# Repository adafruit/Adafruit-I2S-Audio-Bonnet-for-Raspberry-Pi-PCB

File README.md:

## Adafruit I2S Audio Bonnet for Raspberry Pi - UDA1334A PCB

<a href="http://www.adafruit.com/products/4037"><br/>
Click here to purchase one from the Adafruit shop</a>

PCB files for the Adafruit I2S Audio Bonnet for Raspberry Pi - UDA1334A. Format is EagleCAD schematic and board layout
* https://www.adafruit.com/product/4037

### Description

Add some easy-listenin' tunes to your Raspberry Pi using this basic audio bonnet. It'll give you stereo line out from a digital I2S converter for a good price, and sounds nice to boot! This bonnet features the UDA1334A I2S Stereo DAC, a perfect match for any I2S-output audio interface. It's affordable but sounds great - music to our ears.

It's the exact same size as a Raspberry Pi Zero but works with **any and all** Raspberry Pi computers with a 2x20 connector - A+, B+, Zero, Pi 2, Pi 3, etc. We've tested it out with Raspbian (the official operating system) and Retropie.

This Bonnet uses I2S a digital sound standard, so you get really crisp audio. The digital data goes right into the amplifier so there's no static like you hear from the onboard headphone jack. And it's super easy to get started. Just plug in any line level output into powered speakers or audio system. You can plug in headphones but you'll get some distortion - so its best used into something that is expecting line level out

Each order comes as a fully tested and assembled PCB with a 2x20 socket connector. No soldering required! [Plug it right onto your pi, install the script and reboot](https://learn.adafruit.com/adafruit-i2s-audio-bonnet-for-raspberry-pi). Pow, you're makin' lovely sounds. Want an RCA jack output? [We have a solder-in-able stereo jack as a separate component](https://www.adafruit.com/product/4171)

**Pi Zero, audio cable & speakers not included!**

### License

Adafruit invests time and resources providing this open source design, please support Adafruit and open-source hardware by purchasing products from [Adafruit](https://www.adafruit.com)!

Designed by Limor Fried/Ladyada for Adafruit Industries.

Creative Commons Attribution/Share-Alike, all text above must be included in any redistribution. See license.txt for additional details.

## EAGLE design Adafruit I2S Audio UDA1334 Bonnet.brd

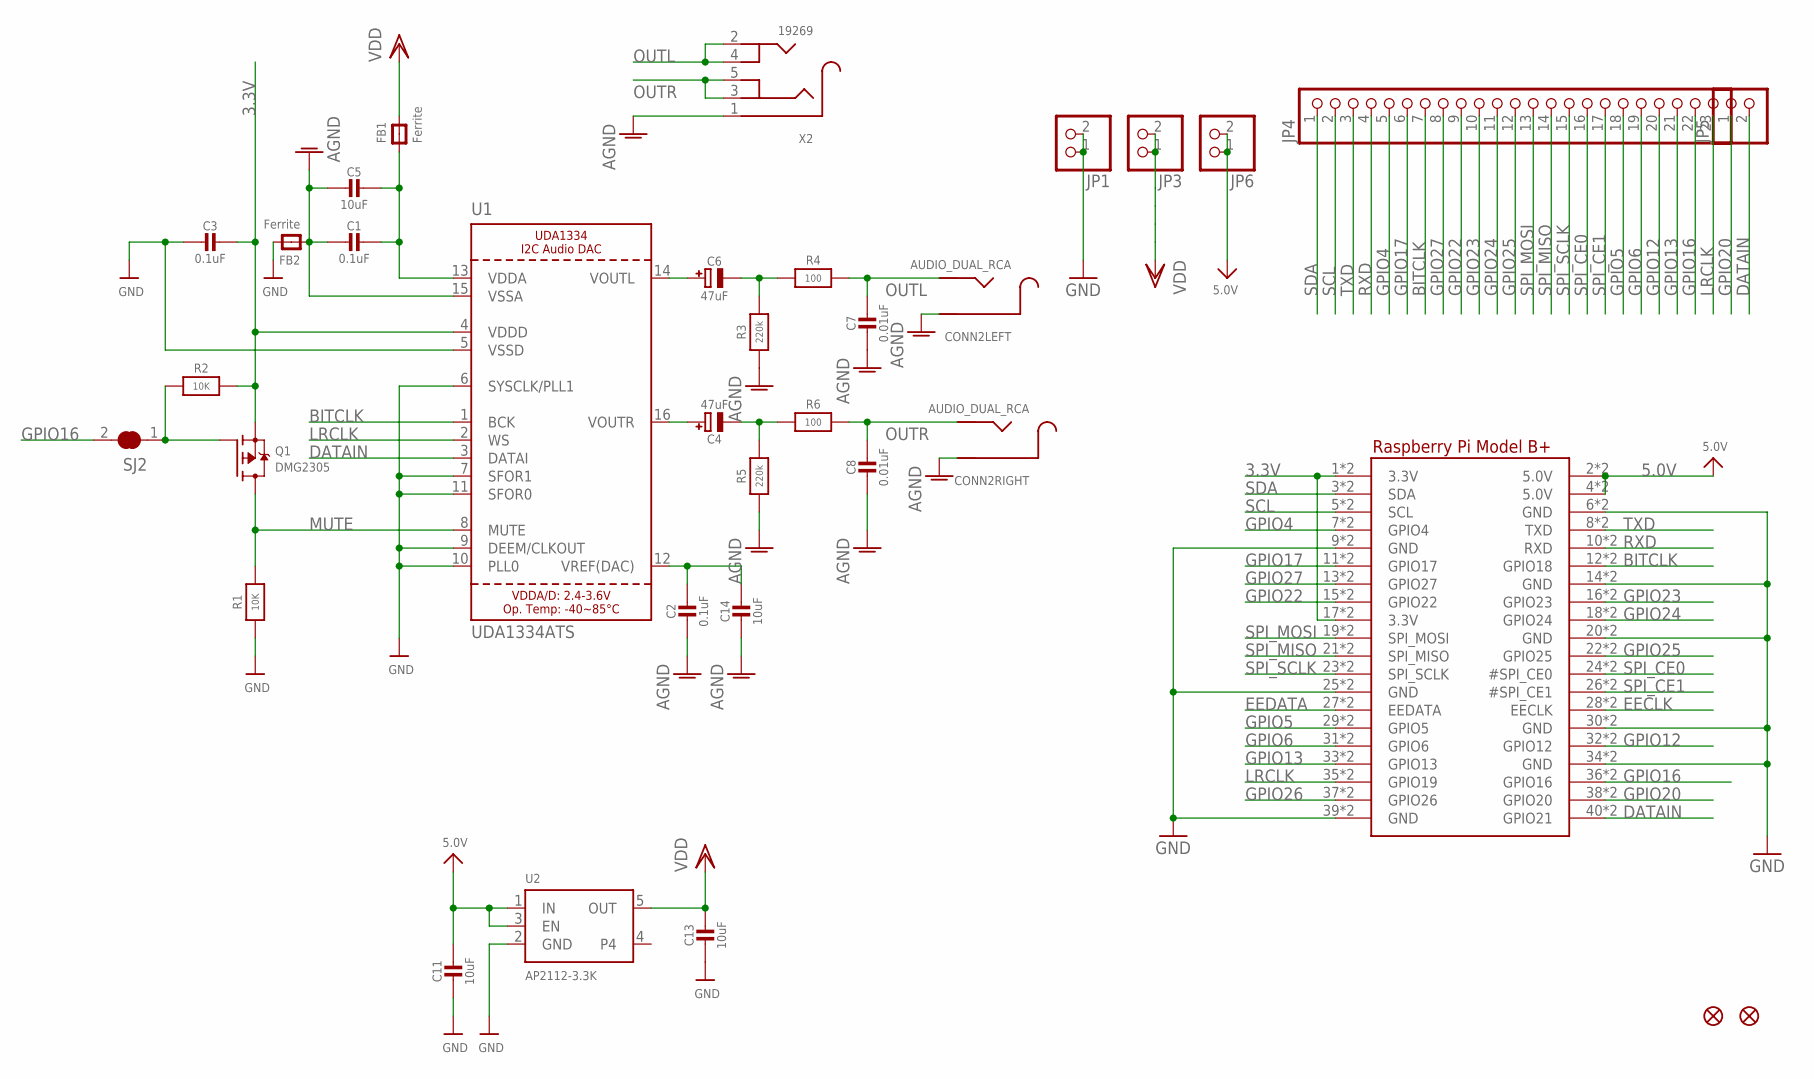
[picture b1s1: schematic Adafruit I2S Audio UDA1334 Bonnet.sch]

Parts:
C1, C2, C3: 0.1uF; 0603-NO
C4, C6: 47uF; PANASONIC_C
C5, C11, C13, C14: 10uF; 0805-NO
C7, C8: 0.01uF; 0603-NO
CONN2: AUDIO_DUAL_RCA; RCA_DUAL_JACK
FB1, FB2: Ferrite; 0805
FID1, FID2: FIDUCIAL_1MM
JP1, JP3, JP5, JP6: HEADER-1X2ROUND; 1X02_ROUND
JP4: HEADER-1X23; 1X23_ROUND_70MIL
Q1: DMG2305; SOT23-WIDE
R1, R2: 10K; 0603-NO
R3, R5: 220k; 0603-NO
R4, R6: 100; 0603-NO
RPI1: RASPBERRYPI_BPLUS_BONNET_THMSMT; PI_BONNET_THMSMT
SJ2: SOLDERJUMPER_CLOSED; SOLDERJUMPER_CLOSEDWIRE
U1: UDA1334ATS; SSOP16_4.4MM
U2: AP2112-3.3K; SOT23-5
X2: 19269; 4UCONN_19269

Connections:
3.3V: C3.1, Q1.2 (S), R2.2, RPI1.1 (3.3V), RPI1.17 (3.3V), RPI1.S1 (3.3V), RPI1.S17 (3.3V), U1.4 (VDDD)
5.0V: C11.1, JP6.1, JP6.2, RPI1.2 (5.0V), RPI1.4 (5.0V), RPI1.S2 (5.0V), RPI1.S4 (5.0V), U2.1 (IN), U2.3 (EN)
AGND: C1.2, C2.2, C5.2, C7.2, C8.2, C14.2, CONN2.L_G (SLEEVE), CONN2.L_G' (SLEEVE), CONN2.R_G (SLEEVE), CONN2.R_G' (SLEEVE), FB2.1, R3.1, R5.1, U1.15 (VSSA), X2.1
BITCLK: JP4.7, RPI1.12 (GPIO18), RPI1.S12 (GPIO18), U1.1 (BCK)
DATAIN: JP5.2, RPI1.40 (GPIO21), RPI1.S40 (GPIO21), U1.3 (DATAI)
EECLK: RPI1.28 (EECLK), RPI1.S28 (EECLK)
EEDATA: RPI1.27 (EEDATA), RPI1.S27 (EEDATA)
GND: C3.2, C11.2, C13.2, FB2.2, JP1.1, JP1.2, R1.1, RPI1.6 (GND), RPI1.9 (GND), RPI1.14 (GND), RPI1.20 (GND), RPI1.25 (GND), RPI1.30 (GND), RPI1.34 (GND), RPI1.39 (GND), RPI1.S6 (GND), RPI1.S9 (GND), RPI1.S14 (GND), RPI1.S20 (GND), RPI1.S25 (GND), RPI1.S30 (GND), RPI1.S34 (GND), RPI1.S39 (GND), U1.5 (VSSD), U1.6 (SYSCLK/PLL1), U1.7 (SFOR1), U1.9 (DEEM/CLKOUT), U1.10 (PLL0), U1.11 (SFOR0), U2.2 (GND)
GPIO4: JP4.5, RPI1.7 (GPIO4), RPI1.S7 (GPIO4)
GPIO5: JP4.18, RPI1.29 (GPIO5), RPI1.S29 (GPIO5)
GPIO6: JP4.19, RPI1.31 (GPIO6), RPI1.S31 (GPIO6)
GPIO12: JP4.20, RPI1.32 (GPIO12), RPI1.S32 (GPIO12)
GPIO13: JP4.21, RPI1.33 (GPIO13), RPI1.S33 (GPIO13)
GPIO16: JP4.22, RPI1.36 (GPIO16), RPI1.S36 (GPIO16), SJ2.2
GPIO17: JP4.6, RPI1.11 (GPIO17), RPI1.S11 (GPIO17)
GPIO20: JP5.1, RPI1.38 (GPIO20), RPI1.S38 (GPIO20)
GPIO22: JP4.9, RPI1.15 (GPIO22), RPI1.S15 (GPIO22)
GPIO23: JP4.10, RPI1.16 (GPIO23), RPI1.S16 (GPIO23)
GPIO24: JP4.11, RPI1.18 (GPIO24), RPI1.S18 (GPIO24)
GPIO25: JP4.12, RPI1.22 (GPIO25), RPI1.S22 (GPIO25)
GPIO26: RPI1.37 (GPIO26), RPI1.S37 (GPIO26)
GPIO27: JP4.8, RPI1.13 (GPIO27), RPI1.S13 (GPIO27)
LRCLK: JP4.23, RPI1.35 (GPIO19), RPI1.S35 (GPIO19), U1.2 (WS)
MUTE: Q1.3 (D), R1.2, U1.8 (MUTE)
unnamed: C2.1, C14.1, U1.12 (VREF(DAC))
unnamed: C1.1, C5.1, FB1.1, U1.13 (VDDA)
unnamed: C4.+, U1.16 (VOUTR)
unnamed: Q1.1 (G), R2.1, SJ2.1
unnamed: C6.+, U1.14 (VOUTL)
unnamed: C6.-, R3.2, R4.1
unnamed: C4.-, R5.2, R6.1
OUTL: C7.1, CONN2.L_SIG (TIP), CONN2.L_SIG' (TIP), R4.2, X2.2, X2.4
OUTR: C8.1, CONN2.R_SIG (TIP), CONN2.R_SIG' (TIP), R6.2, X2.3, X2.5
RXD: JP4.4, RPI1.10 (RXD), RPI1.S10 (RXD)
SCL: JP4.2, RPI1.5 (SCL), RPI1.S5 (SCL)
SDA: JP4.1, RPI1.3 (SDA), RPI1.S3 (SDA)
SPI_CE0: JP4.16, RPI1.24 (#SPI_CE0), RPI1.S24 (#SPI_CE0)
SPI_CE1: JP4.17, RPI1.26 (#SPI_CE1), RPI1.S26 (#SPI_CE1)
SPI_MISO: JP4.14, RPI1.21 (SPI_MISO), RPI1.S21 (SPI_MISO)
SPI_MOSI: JP4.13, RPI1.19 (SPI_MOSI), RPI1.S19 (SPI_MOSI)
SPI_SCLK: JP4.15, RPI1.23 (SPI_SCLK), RPI1.S23 (SPI_SCLK)
TXD: JP4.3, RPI1.8 (TXD), RPI1.S8 (TXD)
VDD: C13.1, FB1.2, JP3.1, JP3.2, U2.5 (OUT)

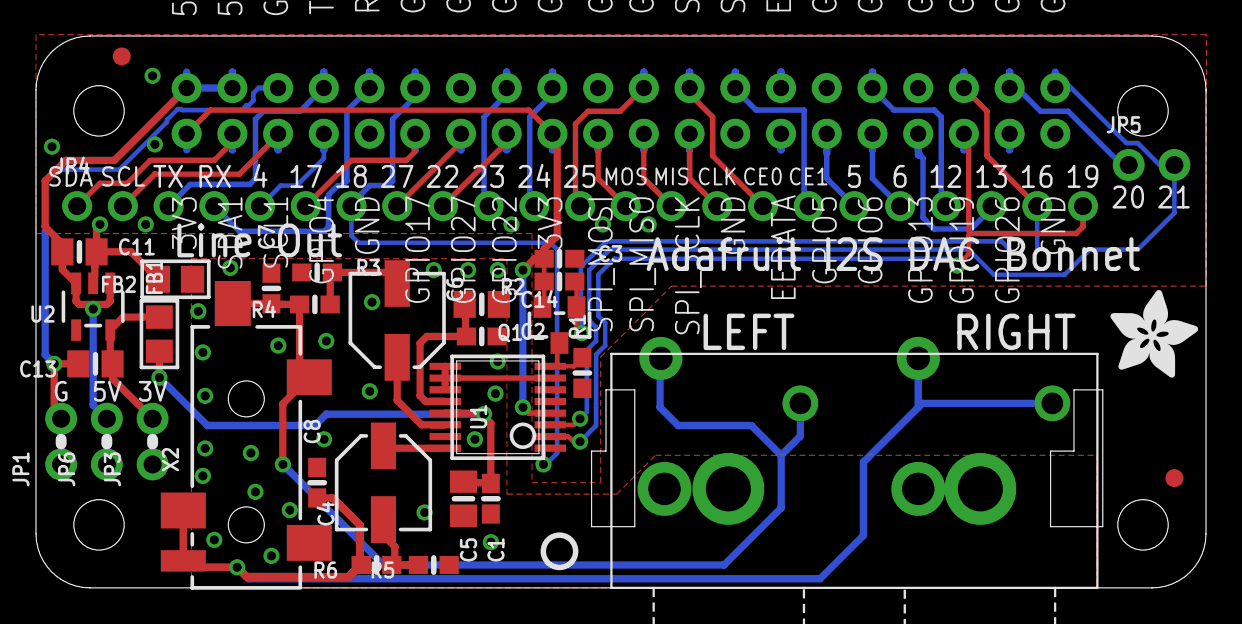
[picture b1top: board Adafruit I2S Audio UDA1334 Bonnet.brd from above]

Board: 2 copper layers, 65.0 x 30.7 mm, 35 parts (1 on the bottom side), 43 nets.

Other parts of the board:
U$5: ADAFRUIT_5MM
U$11: PCBFEAT-REV-040

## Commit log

2018-11-28 init
2018-11-28 fix url
2019-07-16 updated to use cookiecutter for pcb repos

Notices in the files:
parts and their libraries:
microbuilder: This work is placed in the public domain, and may be freely used for commercial and non-commercial work with the following conditions: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
